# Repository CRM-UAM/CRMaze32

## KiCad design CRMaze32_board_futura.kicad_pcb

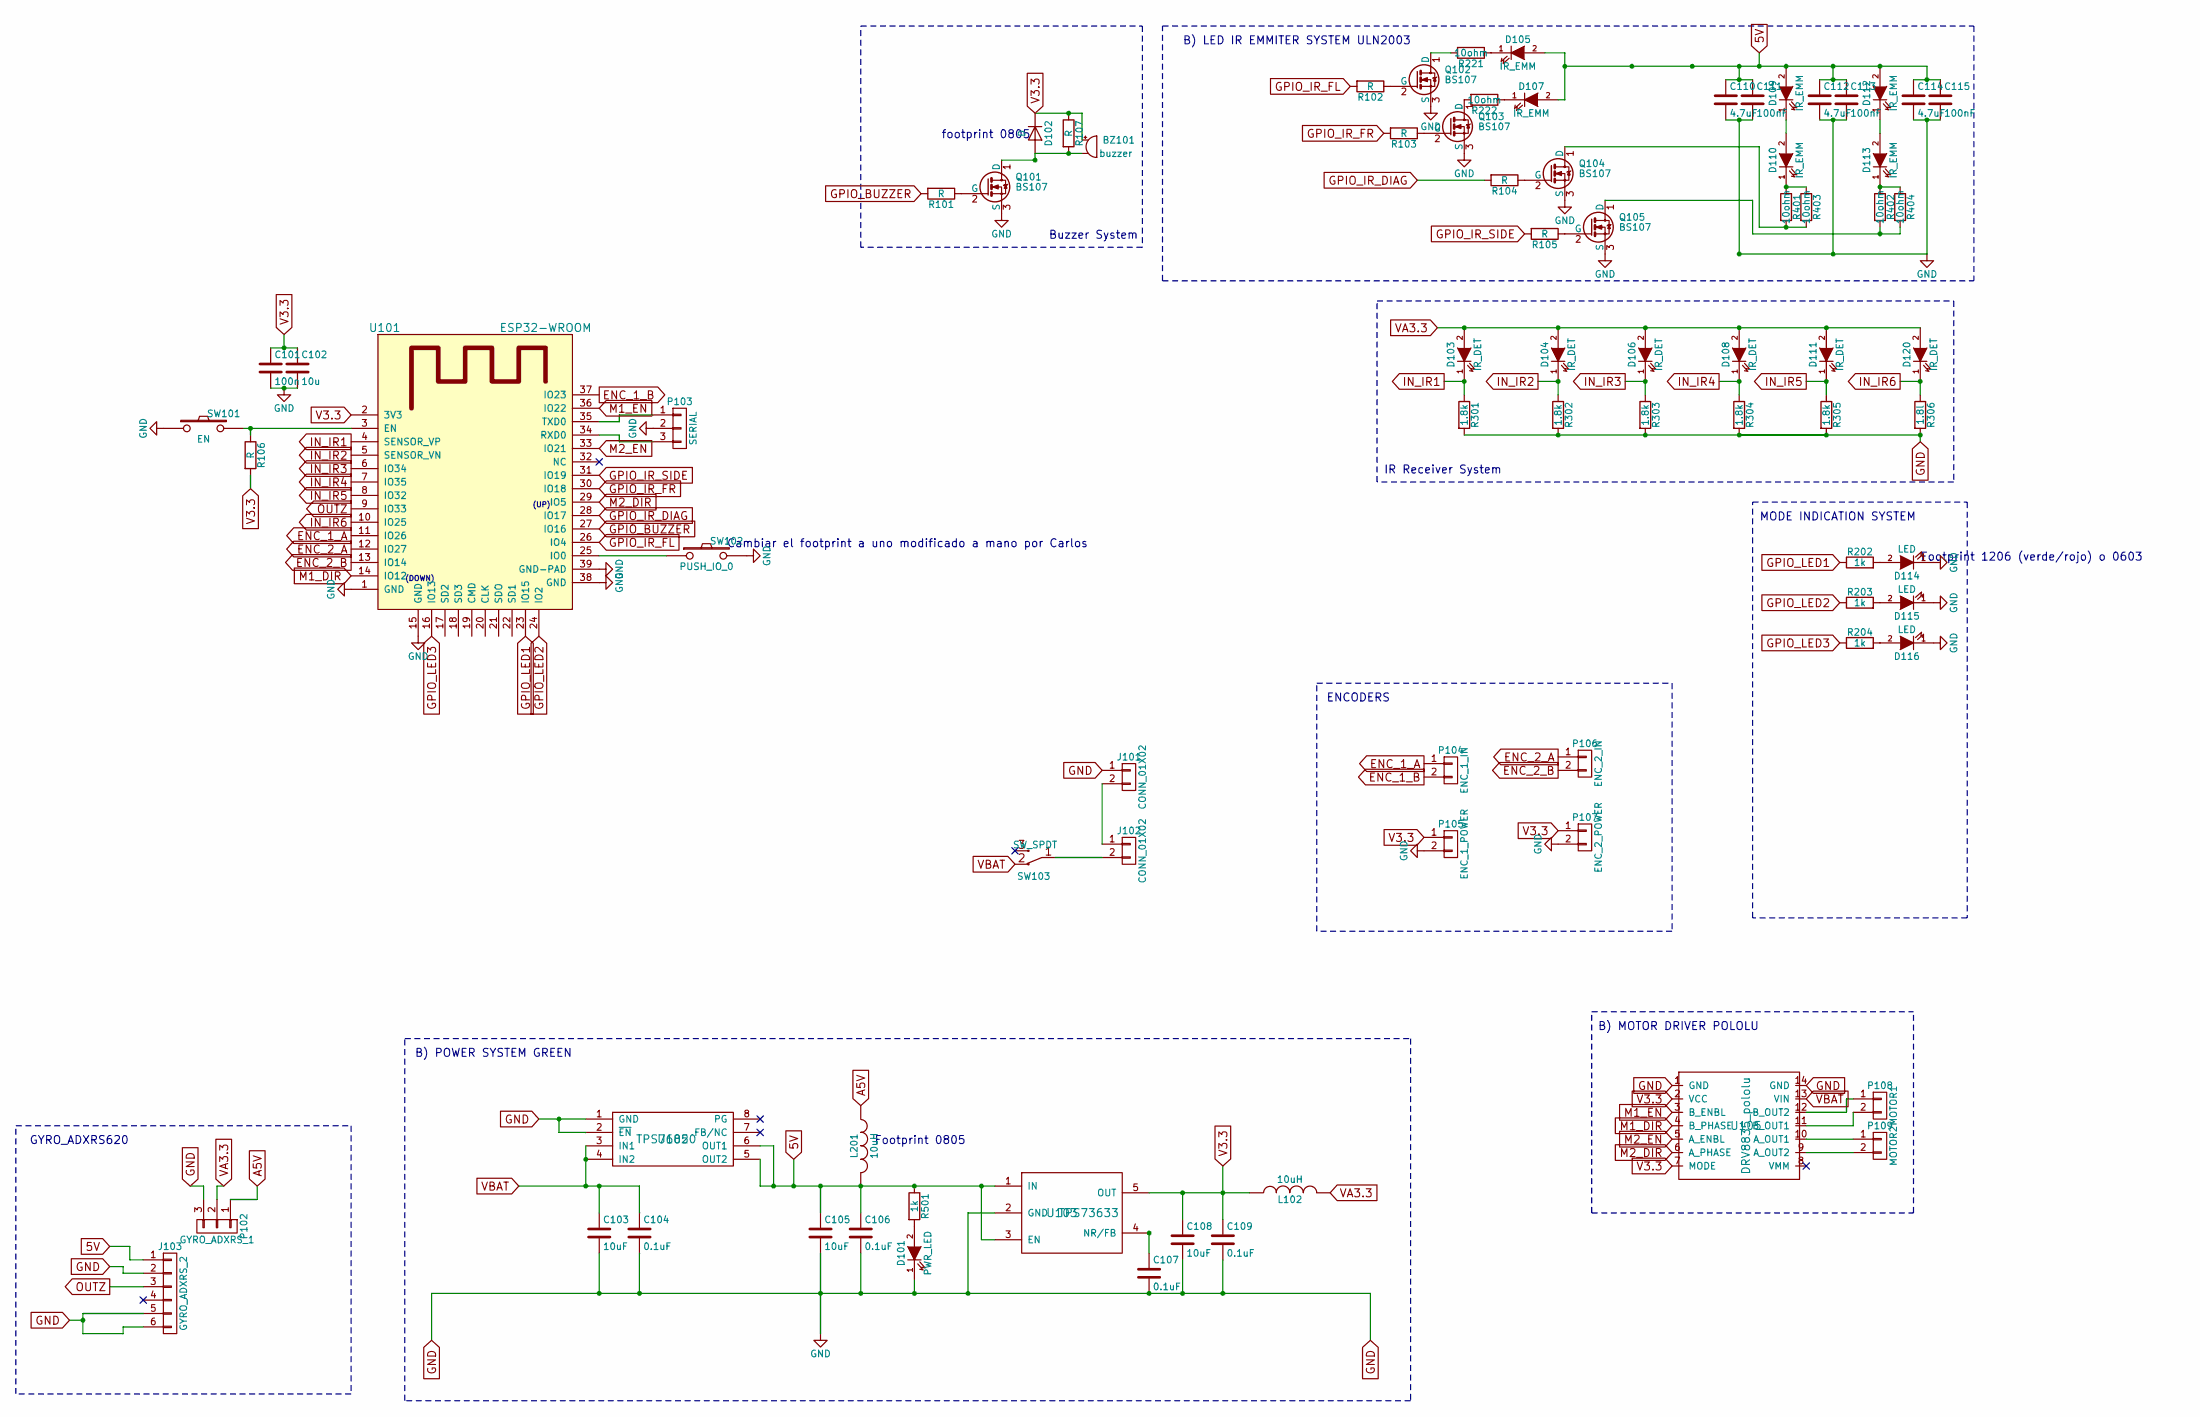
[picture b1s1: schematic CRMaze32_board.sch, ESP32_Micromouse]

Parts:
BZ101: buzzer; c_elec_4x5.8
C101: 100n; C_0805
C102: 10u; C_1206
C103, C105, C108: 10uF; C_1206
C104, C106, C107, C109: 0.1uF; C_0805
C110, C112, C114: 4.7uF; C_1206
C111, C113, C115: 100nF; C_0805
D101: PWR_LED; LED-3MM
D102: D; D_0805
D103, D104, D106, D108, D111, D120: IR_DET; LED-3MM
D105, D107, D109, D110, D112, D113: IR_EMM; LED-3MM
D114, D115, D116: LED; LED_1206
J101, J102: CONN_01X02; Pin_Header_Angled_1x02
J103: GYRO_ADXRS_2; Pin_Header_Straight_1x06
L102, L201: 10uH; L_0805
P102: GYRO_ADXRS_1; Pin_Header_Straight_1x03
P103: SERIAL; Pin_Header_Straight_1x03
P104: ENC_1_IN; Pin_Header_Straight_1x02
P105: ENC_1_POWER; Pin_Header_Straight_1x02
P106: ENC_2_IN; Pin_Header_Straight_1x02
P107: ENC_2_POWER; Pin_Header_Straight_1x02
P108: MOTOR1; Pin_Header_Straight_1x02
P109: MOTOR2; Pin_Header_Straight_1x02
Q101, Q102, Q103, Q104, Q105: BS107; SOT-23
R101, R102, R103, R104, R105, R106, R107: R; R_0805
R202, R203, R204, R501: 1k; R_0805
R221, R222, R401, R402, R403, R404: 10ohm; R_0805
R301, R302, R303, R304, R305: 1.8k; R_0805
R306: 1.8l; R_0805
SW101: EN; smd_button
SW102: PUSH_IO_0; smd_button
SW103: SW_SPDT; switch_power_custom
U101: ESP32-WROOM
U102: TPS76850; SOIC-8-1EP_3.9x4.9mm_Pitch1.27mm
U103: TPS73633; SOT-23-5
U105: DRV8835_pololu; DIP-14_W7.62mm

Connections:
5V: C105.1, C106.1, C110.1, C111.1, C112.1, C113.1, C114.1, C115.1, D105.2 (A), D107.2 (A), D109.2 (A), D112.2 (A), J103.1, L201.2, R501.1, U102.5 (OUT2), U102.6 (OUT1), U103.1 (IN), U103.3 (EN)
A5V: L201.1, P102.1
ENC_1_A: P104.1, U101.11 (IO26)
ENC_1_B: P104.2, U101.37 (IO23)
ENC_2_A: P106.1, U101.12 (IO27)
ENC_2_B: P106.2, U101.13 (IO14)
GND: C101.2, C102.2, C103.2, C104.2, C105.2, C106.2, C107.2, C108.2, C109.2, C110.2, C111.2, C112.2, C113.2, C114.2, C115.2, D101.1 (K), D114.1 (K), D115.1 (K), D116.1 (K), J101.1, J103.2, J103.5, J103.6, P102.3, P103.2, P105.2, P107.2, Q101.3 (S), Q102.3 (S), Q103.3 (S), Q104.3 (S), Q105.3 (S), R301.2, R302.2, R303.2, R304.2, R305.2, R306.2, SW101.1, SW102.2, U101.1 (GND), U101.15 (GND), U101.38 (GND), U101.39 (GND-PAD), U102.1 (GND), U102.2 (~EN), U103.2 (GND), U105.1 (GND), U105.14 (GND)
GPIO_BUZZER: R101.2, U101.27 (IO16)
GPIO_IR_DIAG: R104.2, U101.28 (IO17)
GPIO_IR_FL: R102.2, U101.26 (IO4)
GPIO_IR_FR: R103.2, U101.30 (IO18)
GPIO_IR_SIDE: R105.2, U101.31 (IO19)
GPIO_LED1: R202.1, U101.23 (IO15)
GPIO_LED2: R203.1, U101.24 (IO2)
GPIO_LED3: R204.1, U101.16 (IO13)
IN_IR1: D103.1 (K), R301.1, U101.4 (SENSOR_VP)
IN_IR2: D104.1 (K), R302.1, U101.5 (SENSOR_VN)
IN_IR3: D106.1 (K), R303.1, U101.6 (IO34)
IN_IR4: D108.1 (K), R304.1, U101.7 (IO35)
IN_IR5: D111.1 (K), R305.1, U101.8 (IO32)
IN_IR6: D120.1 (K), R306.1, U101.10 (IO25)
M1_DIR: U101.14 (IO12), U105.4 (B_PHASE)
M1_EN: U101.36 (IO22), U105.3 (B_ENBL)
M2_DIR: U101.29 (IO5), U105.6 (A_PHASE)
M2_EN: U101.33 (IO21), U105.5 (A_ENBL)
unnamed: BZ101.2, D102.2 (A), Q101.1 (D), R107.2
unnamed: C107.1, U103.4 (NR/FB)
unnamed: D101.2 (A), R501.2
unnamed: D105.1 (K), R221.1
unnamed: D107.1 (K), R222.1
unnamed: D109.1 (K), D110.2 (A)
unnamed: D110.1 (K), R401.1, R403.1
unnamed: D112.1 (K), D113.2 (A)
unnamed: D113.1 (K), R402.1, R404.1
unnamed: D114.2 (A), R202.2
unnamed: D115.2 (A), R203.2
unnamed: D116.2 (A), R204.2
unnamed: J101.2, J102.1
unnamed: J102.2, SW103.1 (COM)
unnamed: P103.1, U101.35 (TXD0)
unnamed: P103.3, U101.34 (RXD0)
unnamed: P108.1, U105.12 (B_OUT2)
unnamed: P108.2, U105.11 (B_OUT1)
unnamed: P109.1, U105.10 (A_OUT1)
unnamed: P109.2, U105.9 (A_OUT2)
unnamed: Q101.2 (G), R101.1
unnamed: Q102.1 (D), R221.2
unnamed: Q102.2 (G), R102.1
unnamed: Q103.1 (D), R222.2
unnamed: Q103.2 (G), R103.1
unnamed: Q104.1 (D), R401.2, R403.2
unnamed: Q104.2 (G), R104.1
unnamed: Q105.1 (D), R402.2, R404.2
unnamed: Q105.2 (G), R105.1
unnamed: R106.1, SW101.2, U101.3 (EN)
unnamed: SW102.1, U101.25 (IO0)
OUTZ: J103.3, U101.9 (IO33)
V3.3: BZ101.1, C101.1, C102.1, C108.1, C109.1, D102.1 (K), L102.1, P105.1, P107.1, R106.2, R107.1, U101.2 (3V3), U103.5 (OUT), U105.2 (VCC), U105.7 (MODE)
VA3.3: D103.2 (A), D104.2 (A), D106.2 (A), D108.2 (A), D111.2 (A), D120.2 (A), L102.2, P102.2
VBAT: C103.1, C104.1, SW103.2 (NC), U102.3 (IN1), U102.4 (IN2), U105.13 (VIN)

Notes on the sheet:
Buzzer System
IR Receiver System
GYRO_ADXRS620
B) POWER SYSTEM GREEN
B) LED IR EMMITER SYSTEM ULN2003
B) MOTOR DRIVER POLOLU
MODE INDICATION SYSTEM
ENCODERS
(DOWN)
(UP)
Footprint 1206 (verde/rojo) o 0603
Cambiar el footprint a uno modificado a mano por Carlos
Footprint 0805
footprint 0805

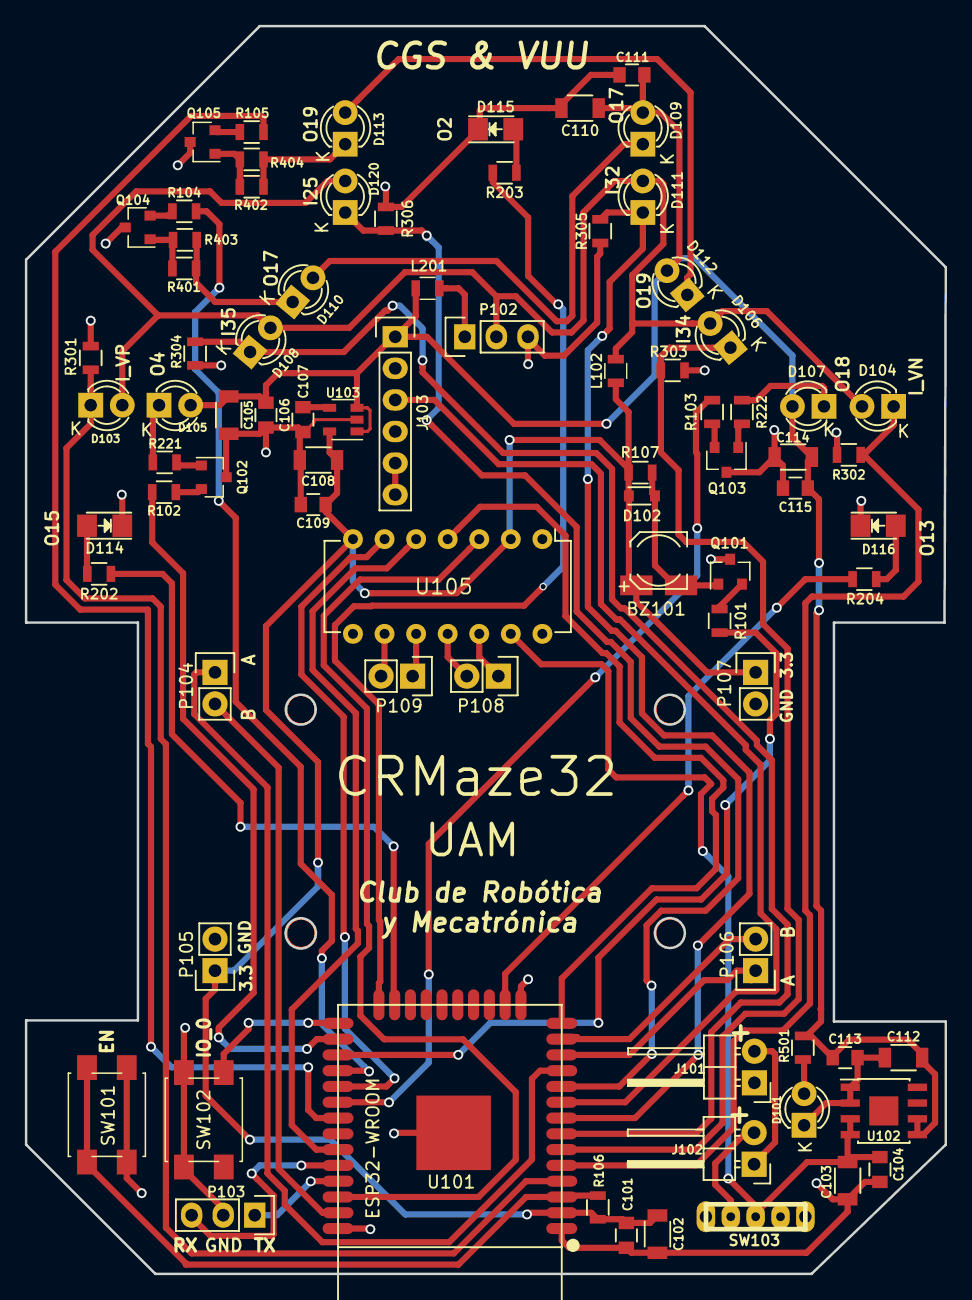
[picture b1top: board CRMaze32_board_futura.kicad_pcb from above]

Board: 2 copper layers, 74.0 x 100.4 mm, 81 parts (0 on the bottom side), 60 nets.

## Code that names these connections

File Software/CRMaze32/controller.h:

#ifndef _SPEED_CONTROLLER_H
#define _SPEED_CONTROLLER_H

#if ARDUINO >= 100
 #include "Arduino.h"
#else
 #include "WProgram.h"
#endif

#define LED_R 13
#define LED_L 15
#define LED_F 2
#define BUZZER_PIN 16

#define O_IR_F_L 4
#define O_IR_F_R 18
#define O_IR_DIA 17
#define O_IR_LAT 19

#define I_IR_F_L 36
#define I_IR_F_R 39
#define I_IR_DIA_L 34
#define I_IR_DIA_R 35
#define I_IR_LAT_L  32
#define I_IR_LAT_R 25

#define LMOTOR_EN 21
#define LMOTOR_CH 6
#define RMOTOR_EN 22
#define RMOTOR_CH 7
#define LMOTOR_DIR 5
#define RMOTOR_DIR 12

#define GYRO 33

#define ENC_1_B 23
#define ENC_1_A 26
#define ENC_2_B 27
#define ENC_2_A 14

#define BUTTON 0

#define DIAMETRO 36.6//17.0 //wheel DIAMETRO in mm
#define TICKS_PER_REV 3510//5000//3540 //ticks resolution of encoder per revolution
#define _PI 3.141592
#define speed_to_counts(v) (TICKS_PER_REV*v/(_PI*DIAMETRO)) // real speed in mm/ms to ticks/ms
#define counts_to_speed(c) ((_PI*DIAMETRO)*c/(TICKS_PER_REV)) // encoder speed in ticks/ms to mm/ms



#define WHEEL_DISTANCE 68
#define ONE_CELL_DISTANCE speed_to_counts(180*2) //18mm to encoder count

#define angSpeed_to_Wcounts(v) (WHEEL_DISTANCE*(v)*_PI*ONE_CELL_DISTANCE/2/180/180/1000)



//PUBLIC var:
extern int targetSpeedX;
extern int targetSpeedW;
extern short onlyUseGyroFeedback;
extern short onlyUseEncoderFeedback;
extern short useEncGyroFeedback;
extern int DLSensor; //Last IR - DL sensor mesure
extern int DRSensor; //Last IR - DR sensor mesure
extern int LFSensor; //Last IR - LF sensor mesure
extern int RFSensor; //Last IR - RF sensor mesure
extern int SRSensor; //Last IR - SR sensor mesure
extern int SLSensor; //Last IR - SL sensor mesure
extern double moveSpeed;
extern int LFvalue2; //to be configured
extern int RFvalue2;

extern int aSpeed;
extern int angle;

extern long oldEncoderCount; //used in move_one_cell
extern long encoderCount;

extern long leftEncoderCount;
extern long rightEncoderCount;

extern double maxSpeed;
extern double moveSpeed;

#define N_TEL 1050
extern int countData;
extern double dataTime[N_TEL];
extern double data1[N_TEL];
extern double data2[N_TEL];
extern double data3[N_TEL];
extern double data4[N_TEL];
extern double data5[N_TEL];
extern double data6[N_TEL];
extern double data7[N_TEL];
extern double data8[N_TEL];
//extern double data9[N_TEL];
//extern double data10[N_TEL];

int readButton();
void allLedsOn();
void allLedsOff();

void readGyro(void);
void readIRsensors();

//speed are in encoder counts/ms, dist is in encoder counts
double needToDecelerate(int32_t dist, int16_t curSpd, int16_t endSpd);


void aligmentFrontWall();

void moveOneCell(short isExploring);
void giro180();
void giro90r();
void giro90l();

void L90();
void L90f();
void R90();
void R90f();
void R180();
void L180f();

void resetSpeedProfile();

void  getSensorEror();
extern int sensorError;
extern int a_scale;

void speedProfile();
void calculateMotorPwm();
void updateCurrentSpeed();
void getEncoderStatus();

void setLeftPwm(int p);
void setRightPwm(int p);

void configQEI_1();
void configQEI_2();
//inline int16_t read_clear_encoder1();
//inline int16_t read_clear_encoder2();

// void encoder_setup();
// void changeEnc2();
// void changeEnc1();
// void changeEnc22();
// void changeEnc11();
//
//
extern int robotDir;
extern int xRobot;
extern int yRobot;
extern int runningFF;
void FFtask(void *a);
void playNoteNoDelay(int freq, int dur);
void elapseMicros(uint32_t targetTime, uint32_t oldt);

#endif

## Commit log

2017-05-28 initial status
2017-06-04 Placa CRMaze_board_futura con forma y componente colocados
2017-06-06 retoques y moificaciones
2017-10-05 esquematico finalizado. Componentes colocados. Comienzo del enrutado.
2017-10-06 avances enrutado
2017-10-06 pre cambio etiquetas esquematico
2017-10-06 arregladas referencias
2017-10-07 enrutado OK
2017-10-07 enrutado finalizado y serigrafia OK
2017-10-08 incluida huella del siwtch a la carpeta local de libs
2017-10-08 cambios minimos serigrafia
2017-11-08 calibrado PID para motores 30:1
2017-11-08 ajustado PID moveOneCell()
2017-11-09 Laberinto de test completado con ajustes de PID
2017-11-09 oshwdem desde madrid
2017-11-12 Codigo competición OSHWDem17
